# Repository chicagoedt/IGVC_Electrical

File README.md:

# IGVC_Electrical
Any Circuit boards or firmware needed for IGVC's electrical systems

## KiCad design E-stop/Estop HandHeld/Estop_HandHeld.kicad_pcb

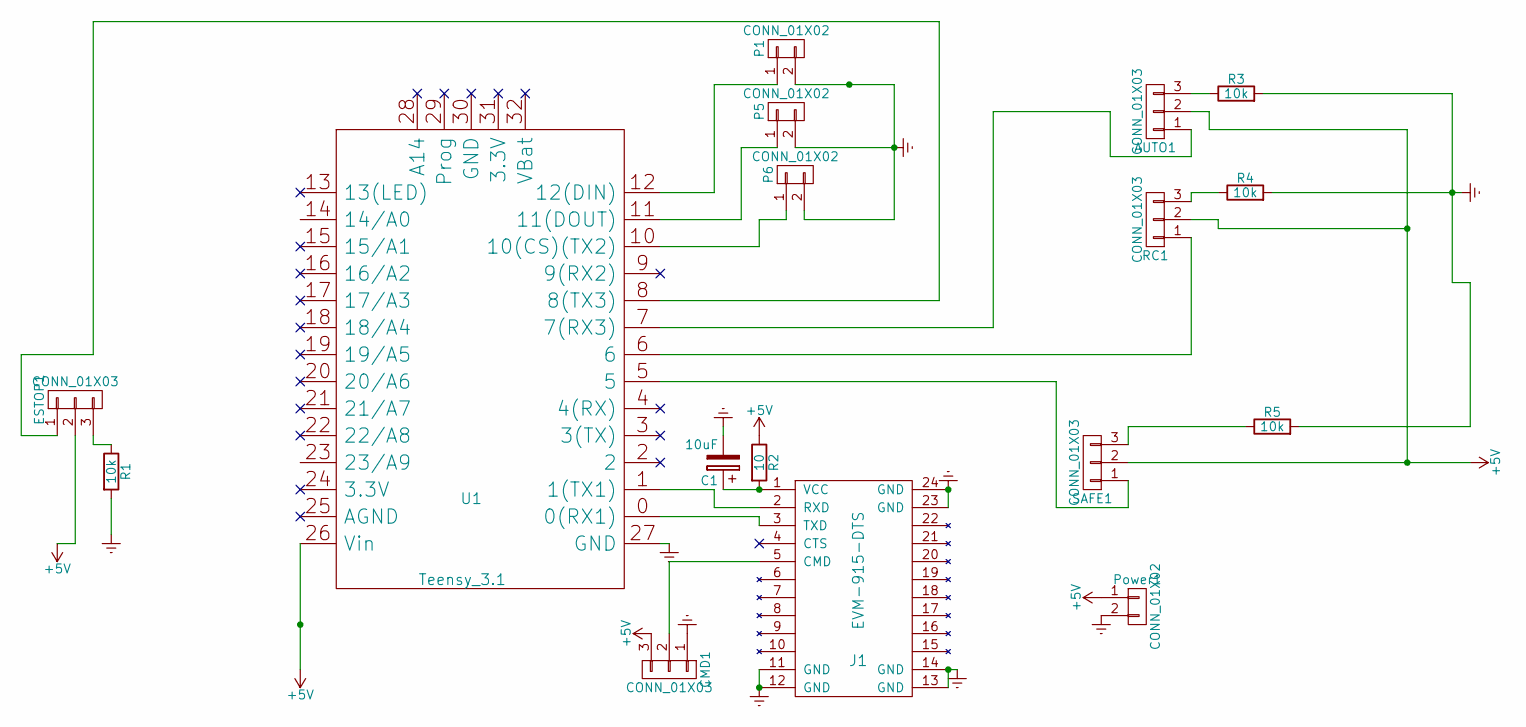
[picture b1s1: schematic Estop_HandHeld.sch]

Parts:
AUTO1: CONN_01X03; Socket_Strip_Straight_1x03
C1: 10uF; CP4
CMD1: CONN_01X03; Socket_Strip_Straight_1x03
ESTOP1: CONN_01X03; Socket_Strip_Straight_1x03
J1: EVM-915-DTS; EVM-915-DTS-Shape
P1, P5, P6: CONN_01X02; Socket_Strip_Straight_1x02
Power1: CONN_01X02; Socket_Strip_Straight_1x02
R1, R3, R4, R5: 10k; Resistor_Horizontal_RM15mm
R2: 10; Resistor_Horizontal_RM15mm
RC1: CONN_01X03; Socket_Strip_Straight_1x03
SAFE1: CONN_01X03; Socket_Strip_Straight_1x03
U1: Teensy_3.1; Teensy-3.1

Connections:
+5V: AUTO1.2, CMD1.3, ESTOP1.2, Power1.1, R2.1, RC1.2, SAFE1.2, U1.26 (Vin)
Earth: C1.2, CMD1.1, J1.11 (GND), J1.12 (GND), J1.13 (GND), J1.14 (GND), J1.23 (GND), J1.24 (GND), P1.2, P5.2, P6.2, Power1.2, R1.2, R3.2, R4.2, R5.2, U1.27 (GND)
unnamed: AUTO1.1, U1.7 (7(RX3))
unnamed: AUTO1.3, R3.1
unnamed: C1.1, J1.1 (VCC), R2.2
unnamed: CMD1.2, J1.5 (CMD)
unnamed: ESTOP1.1, U1.8 (8(TX3))
unnamed: ESTOP1.3, R1.1
unnamed: J1.2 (RXD), U1.1 (1(TX1))
unnamed: J1.3 (TXD), U1.0 (0(RX1))
unnamed: P1.1, U1.12 (12(DIN))
unnamed: P5.1, U1.11 (11(DOUT))
unnamed: P6.1, U1.10 (10(CS)(TX2))
unnamed: R4.1, RC1.3
unnamed: R5.1, SAFE1.3
unnamed: RC1.1, U1.6
unnamed: SAFE1.1, U1.5

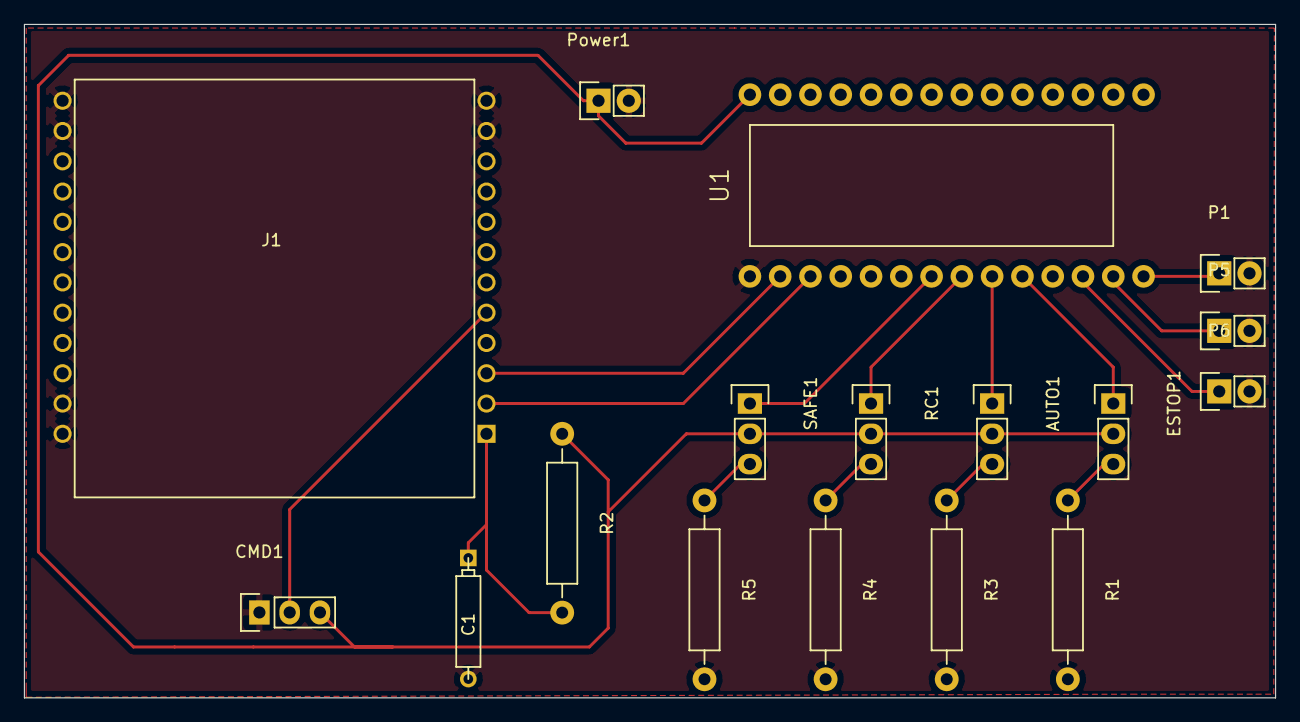
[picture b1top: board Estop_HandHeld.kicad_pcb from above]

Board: 2 copper layers, 105.0 x 56.5 mm, 17 parts (0 on the bottom side), 17 nets.

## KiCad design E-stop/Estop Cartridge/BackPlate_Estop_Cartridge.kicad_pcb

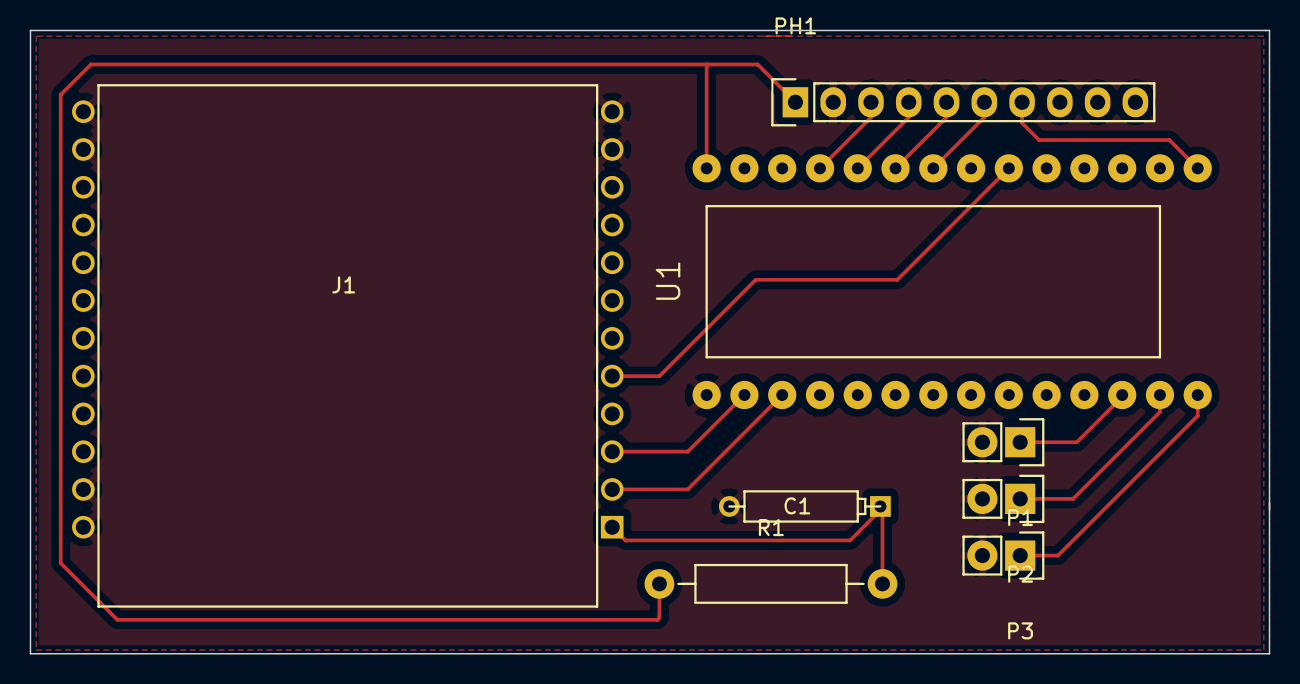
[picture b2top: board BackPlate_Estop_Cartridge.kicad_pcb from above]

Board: 2 copper layers, 83.3 x 41.9 mm, 8 parts (0 on the bottom side), 14 nets.

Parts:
C1: CP; CP4
J1: EVM-915-DTS; EVM-915-DTS-Shape
P1, P2, P3: CONN_01X02; Socket_Strip_Straight_1x02
PH1: CONN_01X10; Socket_Strip_Straight_1x10
R1: 10; Resistor_Horizontal_RM15mm
U1: Teensy_3.1; Teensy-3.1

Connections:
+5V: PH1.1, R1.1, U1.26
Earth: C1.2, J1.11, J1.12, J1.13, J1.14, J1.23, J1.24, P1.2, P2.2, P3.2, PH1.2, U1.27
unnamed: C1.1, J1.1, R1.2
unnamed: J1.2, U1.1
unnamed: J1.3, U1.0
unnamed: J1.5, U1.18
unnamed: P1.1, U1.10
unnamed: P2.1, U1.11
unnamed: P3.1, U1.12
unnamed: PH1.3, U1.23
unnamed: PH1.4, U1.22
unnamed: PH1.5, U1.21
unnamed: PH1.6, U1.20
unnamed: PH1.7, U1.13

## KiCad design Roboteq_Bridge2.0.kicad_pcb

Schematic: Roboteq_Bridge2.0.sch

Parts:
J1: DB25; DB25FC
J2: DB9; DB9FC
P1, P2: CONN_01X05; Pin_Header_Straight_1x05
P3: CONN_01X04; Pin_Header_Straight_1x04
P4, P5, P6, P7: CONN_01X02; Pin_Header_Straight_1x02

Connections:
+5V: J1.14, J1.25, P1.4, P2.4, P3.2
Battery+24V: P4.1, P5.1, P6.1, P7.1
BatteryGND: P4.2, P5.2, P6.2, P7.2
GND: J1.1, J1.5, J1.13, J2.5, P1.1, P2.1, P3.3, P3.4
LEFT_ENC1_A: J1.12, P1.3
LEFT_ENC1_B: J1.24, P1.5
RC1: J1.15, P3.1
RIGHT_ENC2_A: J1.11, P2.3
RIGHT_ENC2_B: J1.23, P2.5
RS232-Rx: J1.3, J2.2
RS232-Tx: J1.2, J2.3

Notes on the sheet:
RC1
Roboteq DB-25
Left Wheel Encoder
Right Wheel Encoder
Blue
Yellow
Orange
Brown
Battery Input 24V
Roboteq Power

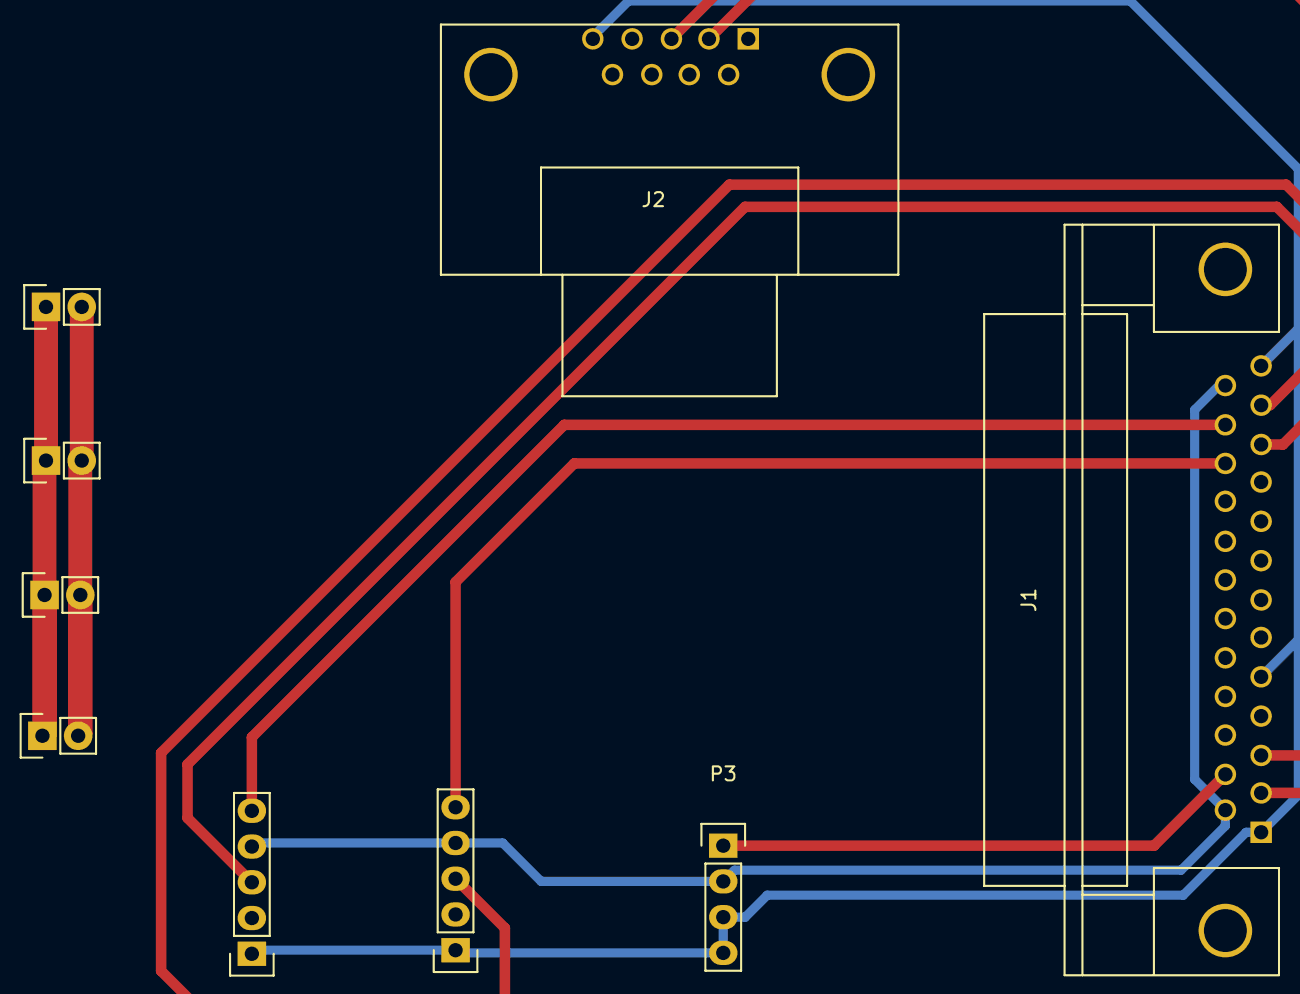
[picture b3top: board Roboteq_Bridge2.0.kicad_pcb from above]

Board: 2 copper layers, 9 parts (0 on the bottom side), 11 nets.

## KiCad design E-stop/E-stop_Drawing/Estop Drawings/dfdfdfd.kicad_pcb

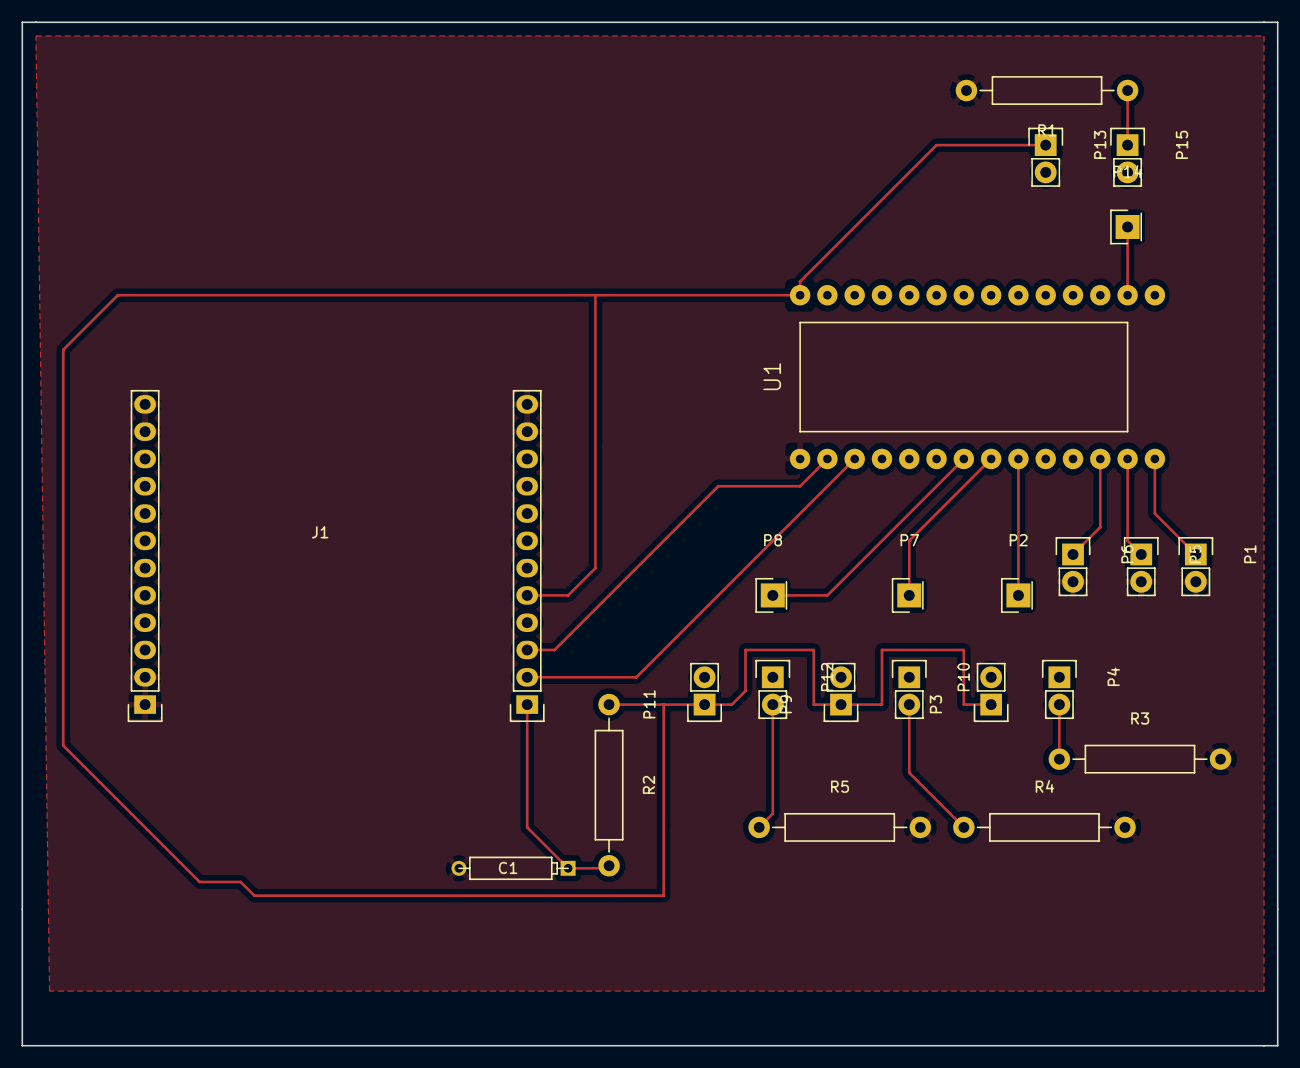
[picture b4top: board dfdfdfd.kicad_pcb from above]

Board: 2 copper layers, 116.8 x 95.2 mm, 23 parts (0 on the bottom side), 16 nets.

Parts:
C1: 10uF; CP4
J1: EVM-915-DTS; EVM-915-DTS_Pin_Header
P1, P3, P4, P5, P6, P9, P10, P11, P12, P13, P15: CONN_01X02; Socket_Strip_Straight_1x02
P2, P7, P8, P14: CONN_01X01; Socket_Strip_Straight_1x01
R1: R; Resistor_Horizontal_RM15mm
R2: 10; Resistor_Horizontal_RM15mm
R3, R4, R5: 10k; Resistor_Horizontal_RM15mm
U1: Teensy_3.1; Teensy-3.1

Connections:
+5V: J1.5, P3.1, P9.1, P11.1, P13.1, R2.1, U1.26
Earth: C1.2, J1.11, J1.12, P1.2, P5.2, P6.2, R1.2, R3.2, R4.2, R5.2, U1.27
unnamed: C1.1, J1.1, R2.2
unnamed: J1.2, U1.1
unnamed: J1.3, U1.0
unnamed: P1.1, U1.12
unnamed: P2.1, U1.7
unnamed: P4.2, R3.1
unnamed: P5.1, U1.11
unnamed: P6.1, U1.10
unnamed: P7.1, U1.6
unnamed: P8.1, U1.5
unnamed: P10.2, R4.1
unnamed: P12.2, R5.1
unnamed: P14.1, U1.14
unnamed: P15.1, R1.1

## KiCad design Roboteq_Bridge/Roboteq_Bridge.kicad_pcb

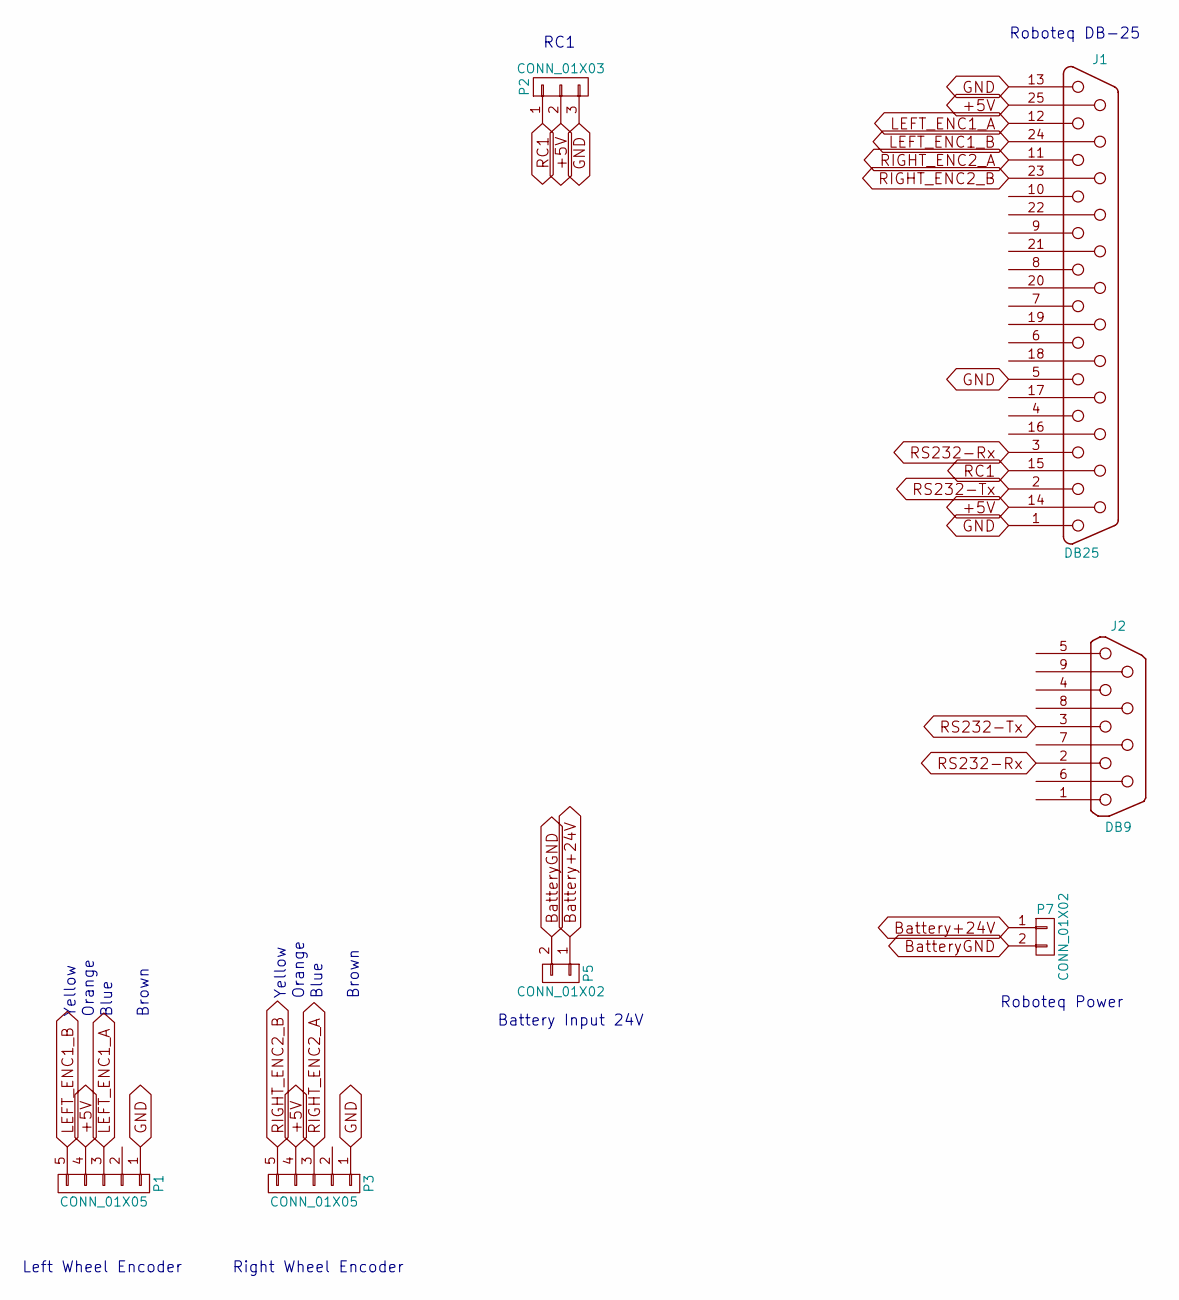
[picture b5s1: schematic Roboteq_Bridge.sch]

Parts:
J1: DB25; DB25FC
J2: DB9; DB9FC
P1, P3: CONN_01X05; Pin_Header_Straight_1x05
P2: CONN_01X03; Pin_Header_Straight_1x03
P5, P7: CONN_01X02; Pin_Header_Straight_1x02

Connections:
+5V: J1.14, J1.25, P1.4, P2.2, P3.4
Battery+24V: P5.1, P7.1
BatteryGND: P5.2, P7.2
GND: J1.1, J1.5, J1.13, P1.1, P2.3, P3.1; also elsewhere on the board
LEFT_ENC1_A: J1.12, P1.3
LEFT_ENC1_B: J1.24, P1.5
unnamed 13: J1.16; also elsewhere on the board
RC1: J1.15, P2.1
RIGHT_ENC2_A: J1.11, P3.3
RIGHT_ENC2_B: J1.23, P3.5
RS232-Rx: J1.3, J2.2
RS232-Tx: J1.2, J2.3

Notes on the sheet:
RC1
Roboteq DB-25
Left Wheel Encoder
Right Wheel Encoder
Blue
Yellow
Orange
Brown
Battery Input 24V
Roboteq Power

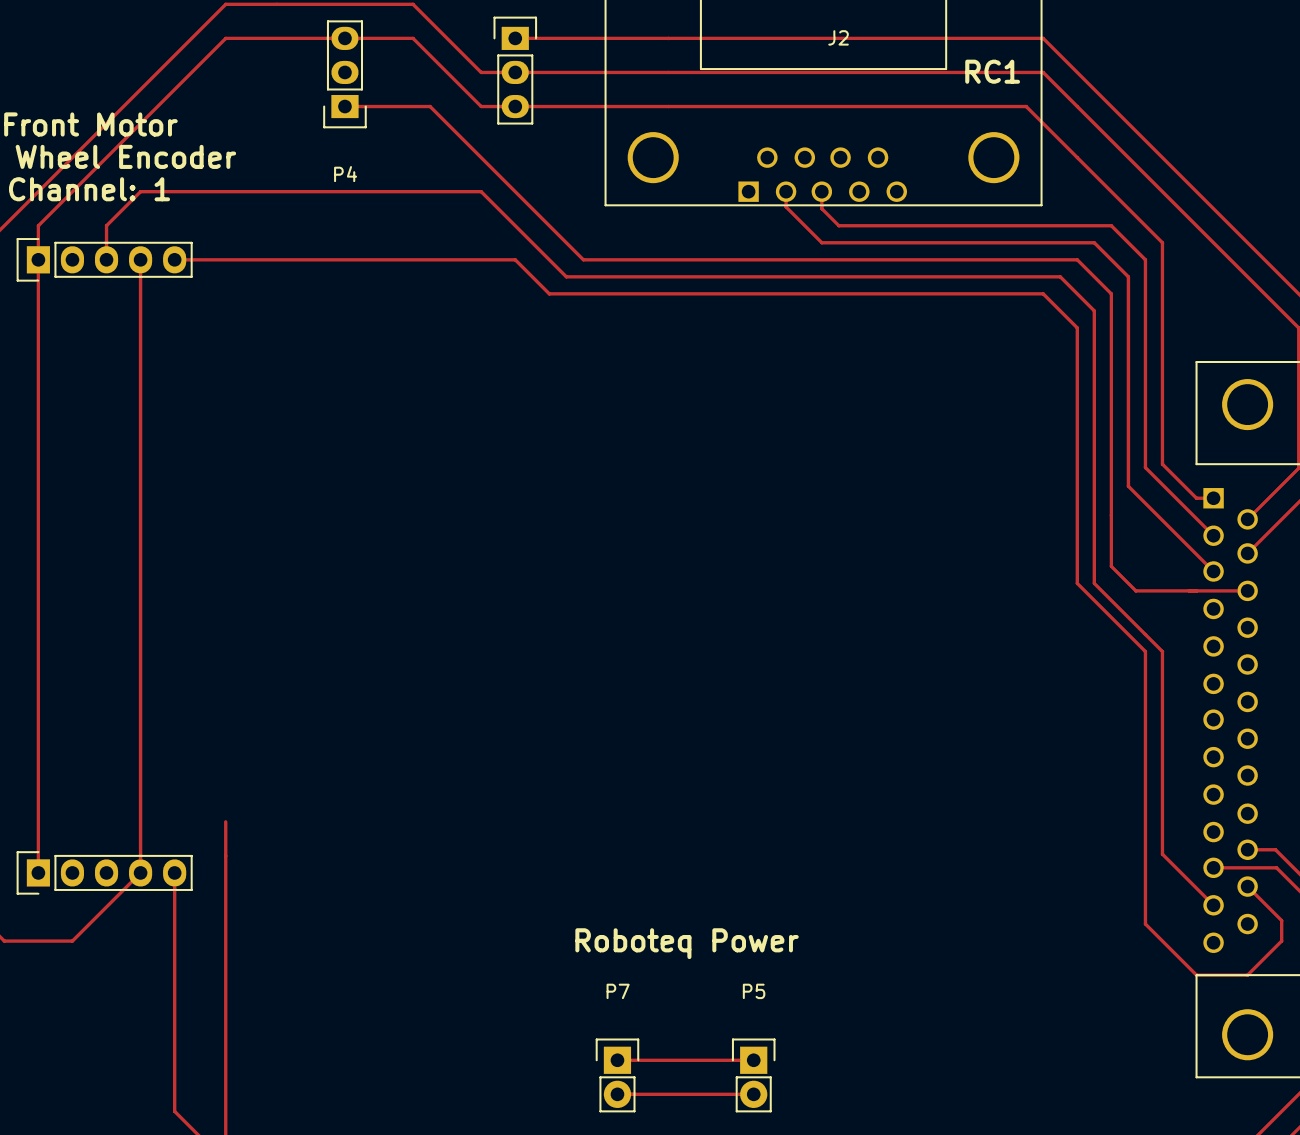
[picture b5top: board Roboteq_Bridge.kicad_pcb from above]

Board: 2 copper layers, 8 parts (0 on the bottom side), 12 nets.

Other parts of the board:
P4: CONN_01X03; Pin_Header_Straight_1x03

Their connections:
GND: P4.3; also elsewhere on the board
unnamed 13: P4.1; also elsewhere on the board

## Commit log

2016-02-24 Added files via upload
2016-02-26 Adding Initial E-stop teensy code
    Bidirectional communication works just between teensy's now.
2016-03-03 Adds test files
2016-03-17 Added files via upload
    Almost finalized, still having issues with molex footprints for 2 pin connectors.
2016-03-17 Added files via upload
    Final Board
2016-03-29 E-stop Drawing Files V-1
2016-04-02 Moved Correctly and more easily readable KiCad into respective folders.
2016-04-05 Estop HandHeld Files updated for Three pin connectors.
2016-04-05 Updated to have Pin for Editing BreadBoard
2016-04-05 Edited to have CMD pin selecter for Code Programing
2016-04-07 V1 Final Kicad Files
